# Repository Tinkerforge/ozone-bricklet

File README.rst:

Ozone Bricklet
==============

**The development of this Bricklet was stopped.**

This repository contains the firmware source code and the hardware design
files. The documentation generator configs can be found at
https://github.com/Tinkerforge/generators

Repository Content
------------------

software/:
 * examples/: Examples for all supported languages
 * build/: Compiled files
 * src/: Source code of firmware
 * Makefile: Makefile to build project

hardware/:
 * Contains KiCad project files and additionally schematics as PDF

datasheets/:
 * Contains datasheets for sensors and complex ICs that are used

Hardware
--------

The hardware is designed with the open source EDA Suite KiCad
(http://www.kicad.org). Before you are able to open the files,
you have to install the Tinkerforge kicad-libraries
(https://github.com/Tinkerforge/kicad-libraries). You can either clone
them directly in hardware/ or clone them in a separate folder and
symlink them into hardware/
(ln -s kicad_path/kicad-libraries project_path/hardware). After that you
can open the .pro file in hardware/ with KiCad and from there view and
modify the schematics and the PCB layout.

Software
--------

If you want to do your own Brick/Bricklet firmware development we highly
recommend that you use our build environment setup script and read the
tutorial (https://www.tinkerforge.com/en/doc/Tutorials/Tutorial_Build_Environment/Tutorial.html).

To compile the C code we recommend you to install the newest GNU Arm Embedded
Toolchain (https://launchpad.net/gcc-arm-embedded/+download).
You also need to install bricklib (https://github.com/Tinkerforge/bricklib)
and brickletlib (https://github.com/Tinkerforge/brickletlib).

You can either clone it directly in software/src/ or clone it in a
separate folder and symlink it into software/src/
(ln -s bricklib_path/bricklib project_path/software/src/ and
ln -s brickletlib_path/brickletlib project_path/software/src/).
Finally make sure to have CMake installed
(http://www.cmake.org/cmake/resources/software.html).

After that you can build the firmware by invoking make in software/.
The firmware (.bin) can then be found in software/build/ and uploaded
with brickv (click button "Flashing" on start screen).

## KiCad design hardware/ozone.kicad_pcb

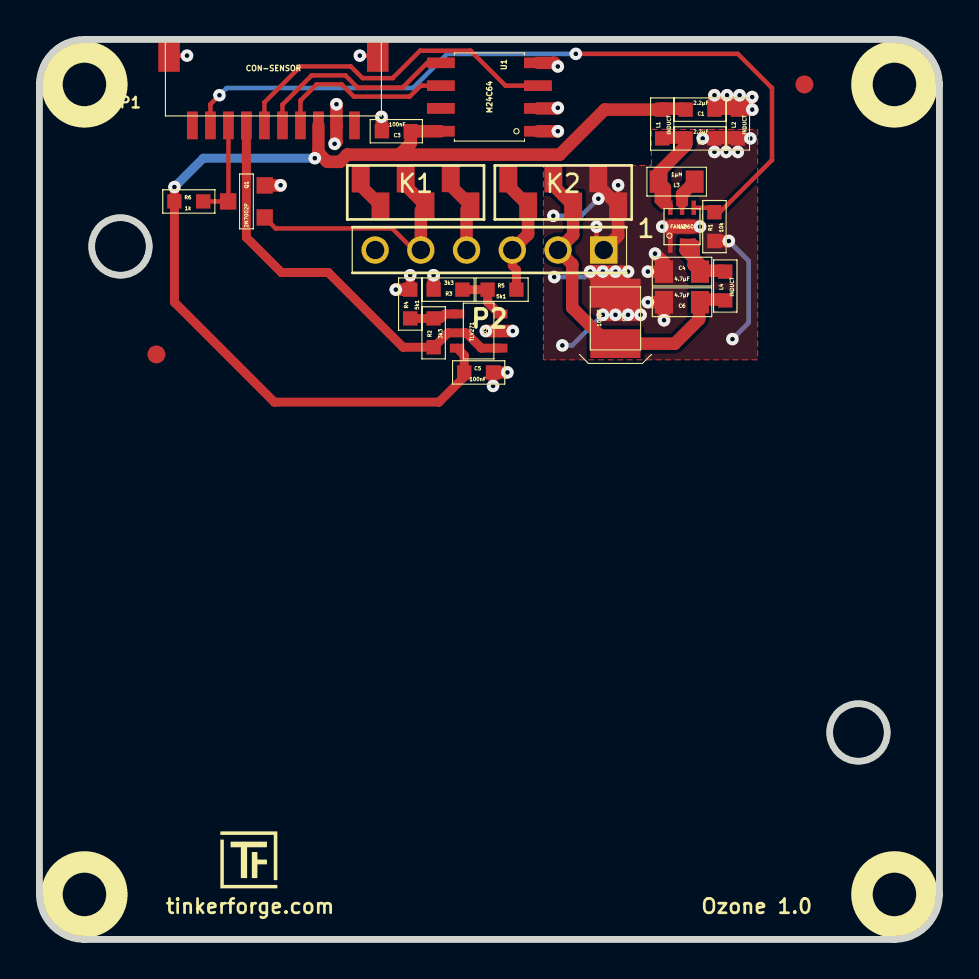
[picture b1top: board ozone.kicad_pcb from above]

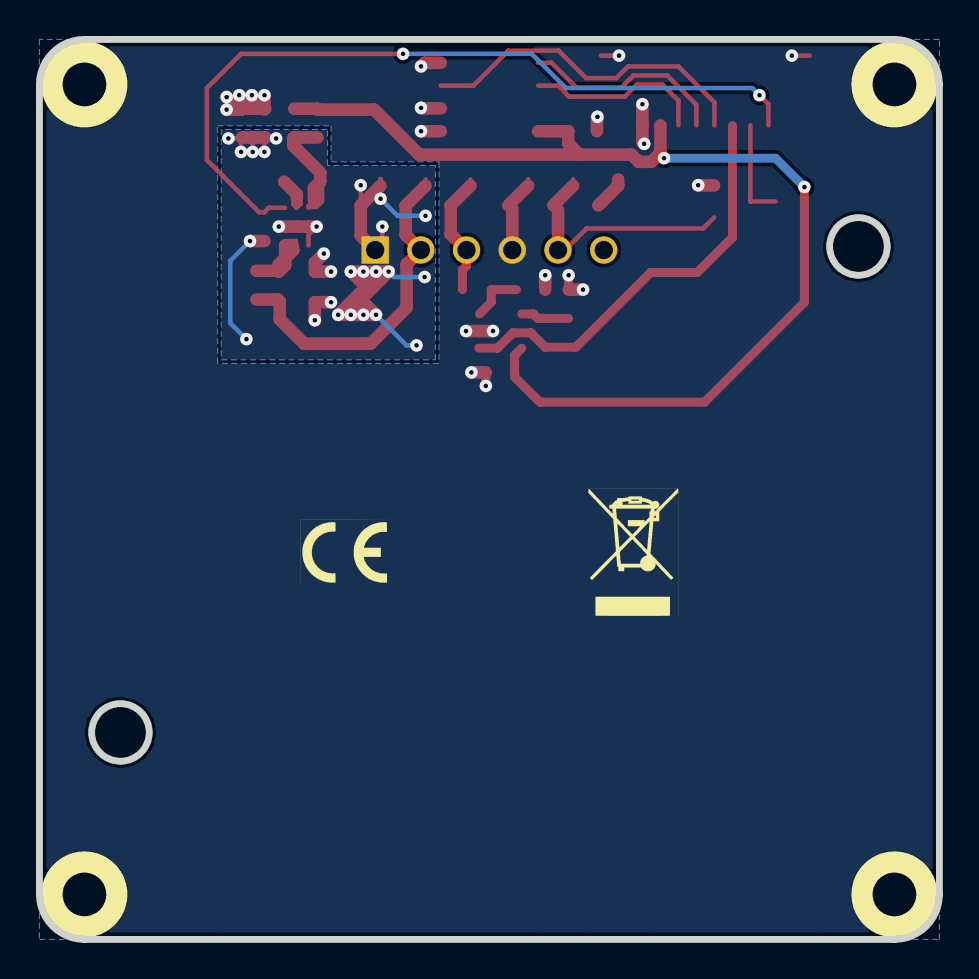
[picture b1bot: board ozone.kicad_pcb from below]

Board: 2 copper layers, 50.0 x 50.0 mm, 33 parts (2 on the bottom side), 17 nets.

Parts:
C1, C2: 2.2µF; 0603
C3, C5: 100nF; 0603
C4, C6: 4.7µF; 0805
C7: 100µF; 3528-21
Fiducial_Mark: VAL**; Fiducial_Mark
Fiducial_Mark#2: VAL**; Fiducial_Mark
K1, K2: CONN_3; 9175-003
L1, L2, L4: INDUCT; 0603
L3: 1µH; 0805
P1: CON-SENSOR
P2: CONN_6; pin_array_6x1
Q1: 2N7002P; SOT23GDS
R1: 10k; 0603
R2, R3: 3k3; 0603
R4, R5: 5k1; 0603
R6: 1k; 0603
U1: M24C64; SOIC8
U2: FAN4860; UMLP_22
U3: TLV271; SOT23-5
U4, U5, U6, U7: DRILL; DRILL_NP
VAL: WEEE_7mm_back
VAL#2: CE_5mm

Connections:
3V3: C1.1, C3.2, C5.2, L1.1, P1.3, R6.2, U1.8, U3.5
+5V: C6.2, C7.1, K2.2, L4.2, P2.2
AGND: C2.2, C4.2, C6.1, C7.2, K2.1, L2.2, P2.1, R1.2, U2.1, U2.EP
EN: P1.9, R1.1, U2.4
GND: C1.2, C3.1, C5.1, K1.1, L2.1, P1.2, P1.EP, P2.4, Q1.S, R3.1, R4.1, U1.1, U1.2, U1.4, U3.2
unnamed: C2.1, L1.2, L3.1, U2.6
unnamed: C4.1, L4.1, U2.2, U2.3
unnamed: K1.2, P2.5, Q1.G
unnamed: K2.3, P2.3, R5.1
unnamed: L3.2, U2.5
unnamed: P1.4, U1.6
unnamed: P1.5, U1.5
unnamed: P1.6, U1.3
unnamed: P1.7, R2.2, U3.1
unnamed: P1.8, Q1.D, R6.1
unnamed: R2.1, R4.2, U3.4
unnamed: R3.2, R5.2, U3.3

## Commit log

2015-05-18 Add first stub implementation of Ozone Bricklet
2015-05-18 Add .gitignore
2015-05-18 Add C examples
2015-05-18 Add C# examples
2015-05-18 Add device identifier
2015-05-19 Add Delphi examples
2015-05-19 Add JavaScript examples
2015-05-19 Add Perl examples
2015-05-19 Add PHP examples
2015-05-19 Add Python examples
2015-05-19 Add Ruby examples
2015-05-19 Add Shell examples
2015-05-19 Add VB.NET examples
2015-05-19 Add Matlab/Octave examples
2015-05-19 Add Mathematica examples
2015-05-19 hardware prototype of ozone bricklet
2015-05-20 fix mounting holes
2015-06-08 add enable for dc/dc converter
2015-06-19 Add readme
2015-06-24 Fix version numbers
2015-06-24 Add LabVIEW examples
    Also clean up other examples.
2015-06-24 Resolve Merge Conflicts
2015-06-24 Add Java examples
2015-06-24 java: Fix typos
2015-06-25 Fix typos in Octave examples
2015-07-08 MATLAB example fixes
2015-07-25 Make JavaScript browser example textarea readonly
2015-07-27 Cleanup C/C++, C#, Java, Python and Ruby examples
2015-07-29 Reformat changelog
2015-08-07 Use full device class name in Python examples
2015-08-12 Fix minor warnings in C/C++ examples
2015-08-13 Use correct simple value type
2015-08-14 Cleanup Delphi examples
2015-08-18 Cleanup VB.NET examples
2015-08-19 Cleanup Perl examples
2015-08-20 Fix range type in Java example
2015-08-21 Use shorter print statement in Perl example
2015-09-10 Duplicate cmake call to fix bug during cmake creation
    Also, toolchain is now in bricklib.
2015-09-30 Generator based example cleanup
2015-11-12 matlab: Fix callback handling for R2014a
    http://undocumentedmatlab.com/blog/matlab-callbacks-for-java-events-in-r2014a
2015-11-25 Include date and commit into changelog
2015-11-30 vbnet: Break long line
2016-05-18 c: Add missing device destroy call
2016-06-29 Whitespace
2016-07-01 Make the change UID comment more explicit
2016-07-04 Remove unused define
2017-04-13 csharp: Adapt example
2017-06-02 octave: Use javaObject instead of deprecated java_new
2017-11-30 Update examples from generator
2017-12-07 mathematica: Also generate .nb files
2018-01-26 c: Fine-tune printf format
2018-02-02 Update examples
2018-02-19 javascript: Close div tag correctly
2018-02-20 Cleanup KiCad libraries config
    Ensure LibDir=kicad-libraries and LibName1=tinkerforge.
    Remove special library.
2018-05-24 perl: Use strict in examples
2018-06-28 Fix readme
2018-07-13 Add Makefile with docker support
2018-07-13 Update directory structure and build instructions
2018-07-13 Remove obsolete generate_makefile scripts
2018-09-14 vbnet: Fix typo in comment
2018-11-06 Add rust examples
2018-11-07 rust: Accept host names for ip connection, fix naming inconsistencies
2018-11-07 rust: Rename callback receivers.
2018-12-14 Add go examples.
2018-12-18 go: Change import path.
2018-12-18 go: Change import path again.
2018-12-20 rust: Reformat examples.
2019-01-24 mqtt: Add examples.
2019-01-24 mqtt: Fix example header.
2019-01-24 mqtt: Remove executable bit in example permissions.
2019-01-24 go: Minor example fixes.
2019-01-24 mqtt: Minor example fixes.
2019-03-28 mqtt: Fix whitespace.
2019-08-22 c: Adapt to bindings changes
2019-12-02 Remove examples
2019-12-02 Mark development as stopped
2020-01-13 examples: mqtt: Remove trailing whitespace.
2021-10-25 Update KiCad link
    https://www.kicad.org/blog/2021/10/Avoid-links-to-former-kicad-domain/
2022-07-06 Add license files.

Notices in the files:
hardware/ozone.kicad_pcb:
Licensed under CERN OHL v.1.1
Copyright (©) 2015, B.Nordmeyer
